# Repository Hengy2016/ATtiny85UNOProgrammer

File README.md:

#ATtiny85 UNO programmer

Simple little board for an ATtiny85 programmer for a UNO (plugs directly into the UNO )

Status LEDs are based on the default pinouts in ATTinyCore board as per the ArduinoISP example sketch
copied here :
>
>// Put an LED (with resistor) on the following pins:
>
>// 9: Heartbeat   - shows the programmer is running
>
>// 8: Error       - Lights up if something goes wrong (use red if that makes sense)
>
>// 7: Programming - In communication with the target
>

Really simple circuit

Select resistors to give your prefered LED brightness.

Capacitor values are as recommended but anything similar will work - i used 47 uF for the electrolytic and it was fine. 

The blue LED is on the ATtiny85 digital pin 3 - I use it as a quick check that the an ATtiny85 is ok by uploading a script that pulses that output. I also tend to use that pin as a digital out so it is a good visual check that the chip has been programmed successfully.

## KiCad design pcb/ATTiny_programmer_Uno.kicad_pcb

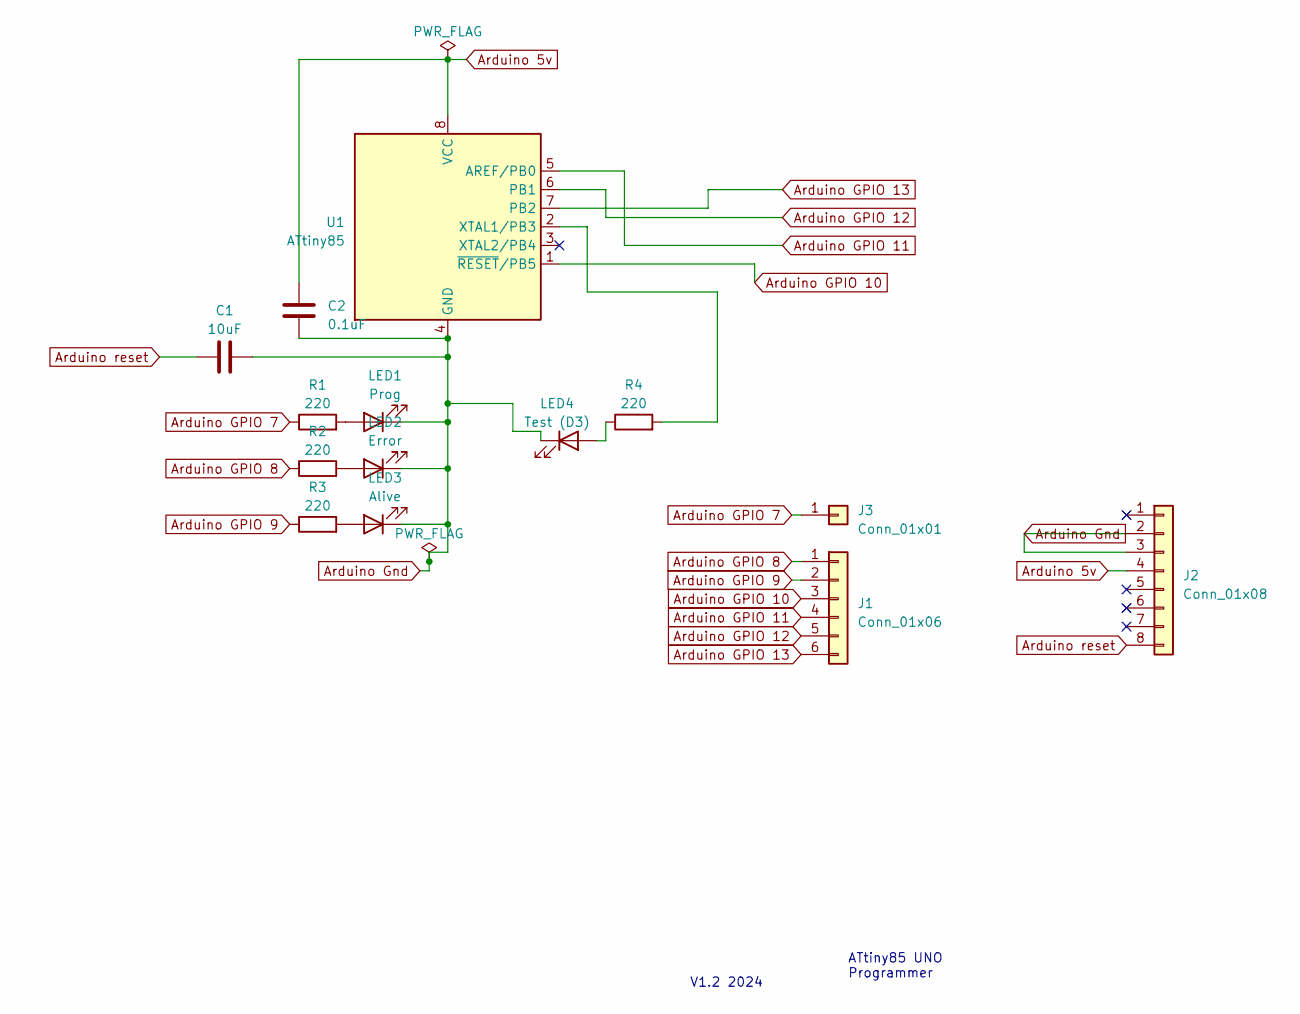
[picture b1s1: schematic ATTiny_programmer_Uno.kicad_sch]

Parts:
C1: 10uF; CP_Radial_P2.5mm
C2: 0.1uF; C_Rect_L7.0mm_W2.5mm_P5.00mm
J1: Conn_01x06; PinHeader_1x06_P2.54mm_Vertical
J2: Conn_01x08; PinHeader_1x08_P2.54mm_Vertical
J3: Conn_01x01; PinHeader_1x01_P2.00mm_Vertical
LED1: Prog; LED_3mm_C1A2
LED2: Error; LED_3mm_C1A2
LED3: Alive; LED_3mm_C1A2
LED4: Test (D3); LED_3mm_C1A2
R1, R2, R3, R4: 220; R_Axial_DIN0207_L6.3mm_D2.5mm_P10.16mm_Horizontal
U1: ATtiny85; DIP-8_W7.62mm

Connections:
Arduino 5v: C2.1, J2.4, U1.8 (VCC)
Arduino GPIO 7: J3.1, R1.1
Arduino GPIO 8: J1.1, R2.1
Arduino GPIO 9: J1.2, R3.1
Arduino GPIO 10: J1.3, U1.1 (~RESET/PB5)
Arduino GPIO 11: J1.4, U1.5 (AREF/PB0)
Arduino GPIO 12: J1.5, U1.6 (PB1)
Arduino GPIO 13: J1.6, U1.7 (PB2)
Arduino Gnd: C1.2, C2.2, J2.2, J2.3, LED1.1 (K), LED2.1 (K), LED3.1 (K), LED4.1 (K), U1.4 (GND)
Arduino reset: C1.1, J2.8
unnamed: LED1.2 (A), R1.2
unnamed: LED2.2 (A), R2.2
unnamed: LED3.2 (A), R3.2
unnamed: LED4.2 (A), R4.1
unnamed: R4.2, U1.2 (XTAL1/PB3)

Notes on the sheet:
V1.2 2024
ATtiny85 UNO Programmer

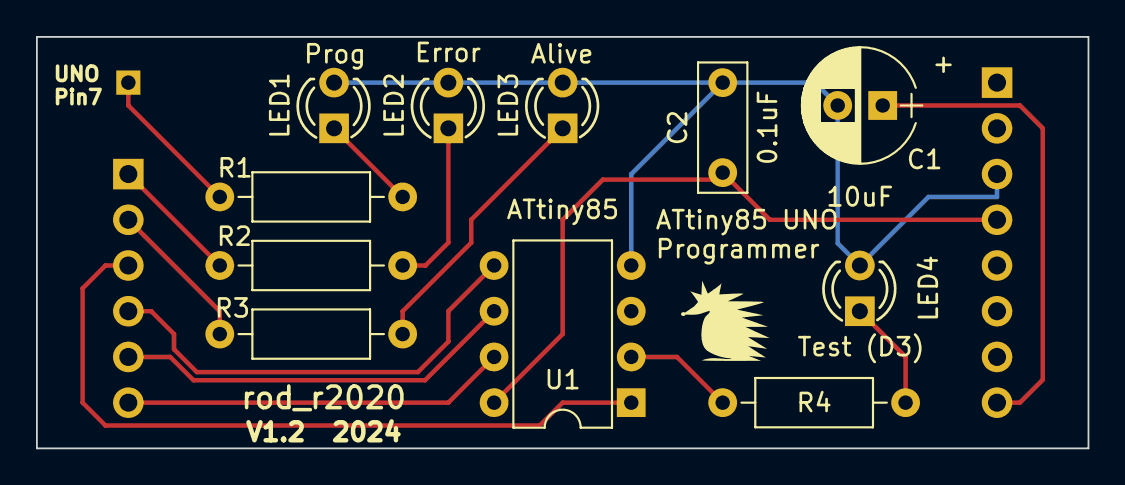
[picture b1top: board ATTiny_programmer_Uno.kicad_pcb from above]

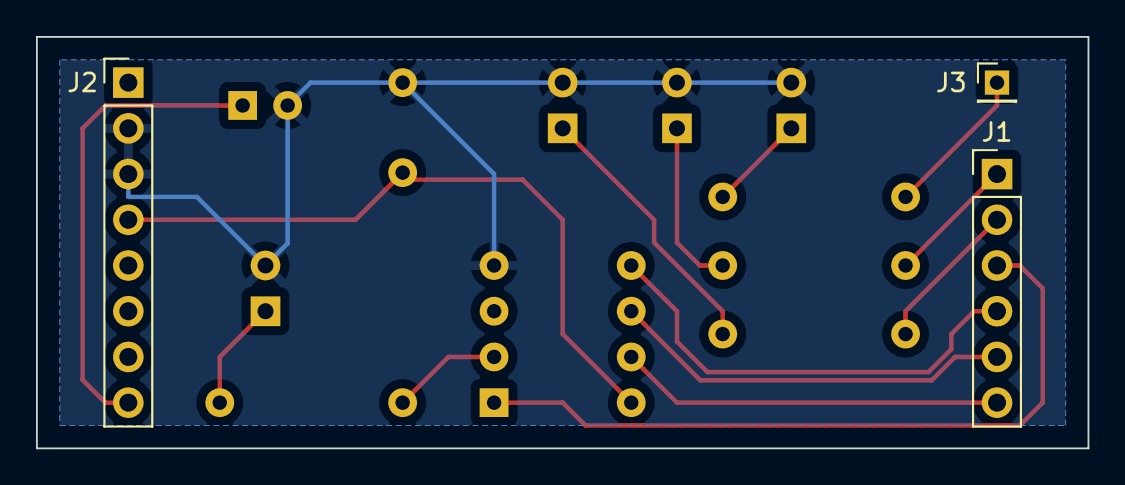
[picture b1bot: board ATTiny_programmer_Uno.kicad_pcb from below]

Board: 2 copper layers, 58.4 x 22.9 mm, 14 parts (3 on the bottom side), 15 nets.

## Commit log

2024-01-19 Added test sketch
